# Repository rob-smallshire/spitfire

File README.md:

# SPItFIRE

**SPI + joystick FIRE button** - An analogue joystick and quadrature mouse adapter for the Acorn BBC Master Compact.

## Overview

The Acorn BBC Master Compact lacks the analogue-to-digital converter (ADC) hardware found in other BBC Micro models, making it incompatible with standard analogue joysticks. SPItFIRE bridges this gap by providing:

- **Analogue joystick support** via ADC sampling of potentiometer positions
- **Peripheral DE-9 port** for connecting a quadrature mouse (or other devices)
- **Keyboard matrix scanning** for joystick buttons

The system uses an ATMega1284p microcontroller as an SPI slave device. The BBC Master Compact's Mouse/Joystick port (an exposed 6522 VIA) communicates with the microcontroller via a bit-banged SPI protocol.

## Architecture

```
                               Host DE-9
┌─────────────────────┐         SPI          ┌──────────────────────┐
│  BBC Master Compact │◄────────────────────►│     ATMega1284p      │
│                     │   (bit-banged on     │                      │
│  6522 VIA Port      │    User VIA Port B)  │  ┌────────────────┐  │
└─────────────────────┘                      │  │ ADC: Joystick  │  │
                                             │  │ GPIO: Buttons  │  │
                                             │  │ GPIO: Mouse    │  │
                                             │  └────────────────┘  │
                                             └──────────────────────┘
                                                      │
                       ┌──────────────────────┬───────┴───────┐
                       ▼                      ▼               ▼
                 ┌──────────┐          ┌──────────┐   ┌──────────────┐
                 │ Joystick │          │  Keypad  │   │ Peripheral   │
                 │ (Analog) │          │  Matrix  │   │    DE-9      │
                 │  DA-15   │          │          │   │ Mouse/Serial │
                 └──────────┘          └──────────┘   └──────────────┘
```

## Repository Structure

```
spitfire/
├── firmware/           ATMega1284p C++ firmware (SPI slave)
│   ├── src/            Source files
│   ├── include/        Header files
│   ├── cmake/          CMake toolchain files
│   ├── CMakeLists.txt  Build configuration
│   └── CMakePresets.json
├── rom/                BBC Micro 6502 assembly ROM driver
│   └── src/            BeebAsm source files
├── hardware/           KiCAD hardware designs
│   └── spitfire/       Main schematic and PCB
└── docs/               Documentation
    └── protocol.md     SPI protocol specification
```

## Building

### Firmware (ATMega1284p)

Requirements:
- CMake 3.20+
- avr-gcc toolchain
- avrdude (for programming)

```bash
cd firmware
cmake --preset release
cmake --build --preset release
cmake --build --preset release --target upload
```

### ROM (BBC Micro)

Requirements:
- BeebAsm assembler

```bash
cd rom
make
```

## Hardware

The hardware design is created in KiCAD. See the `hardware/` directory for schematics and PCB layouts.

### Connectors

SPItFIRE has two DE-9 connectors:

- **Host DE-9**: Connects to BBC Master Compact's Mouse/Joystick port (exposes 6522 VIA). Carries SPI bus signals and device selection.
- **Peripheral DE-9**: Directly connects input devices to SPItFIRE. Directly accepts quadrature mice, switched joysticks, or serial devices. Connected to AVR Port D.

### Additional Connections

- **Joystick Inputs**: Two DA-15 ports for analogue joysticks (directly via ADC channels)

## Protocol

The BBC Micro bit-bangs an SPI protocol on the VIA port to:
- Configure the adapter
- Request joystick position data (X/Y axes)
- Request mouse velocity data
- Read button states

See [docs/protocol.md](docs/protocol.md) for the full protocol specification.

## License

This project is licensed under the GNU General Public License v3.0 - see the [LICENSE](LICENSE) file for details.

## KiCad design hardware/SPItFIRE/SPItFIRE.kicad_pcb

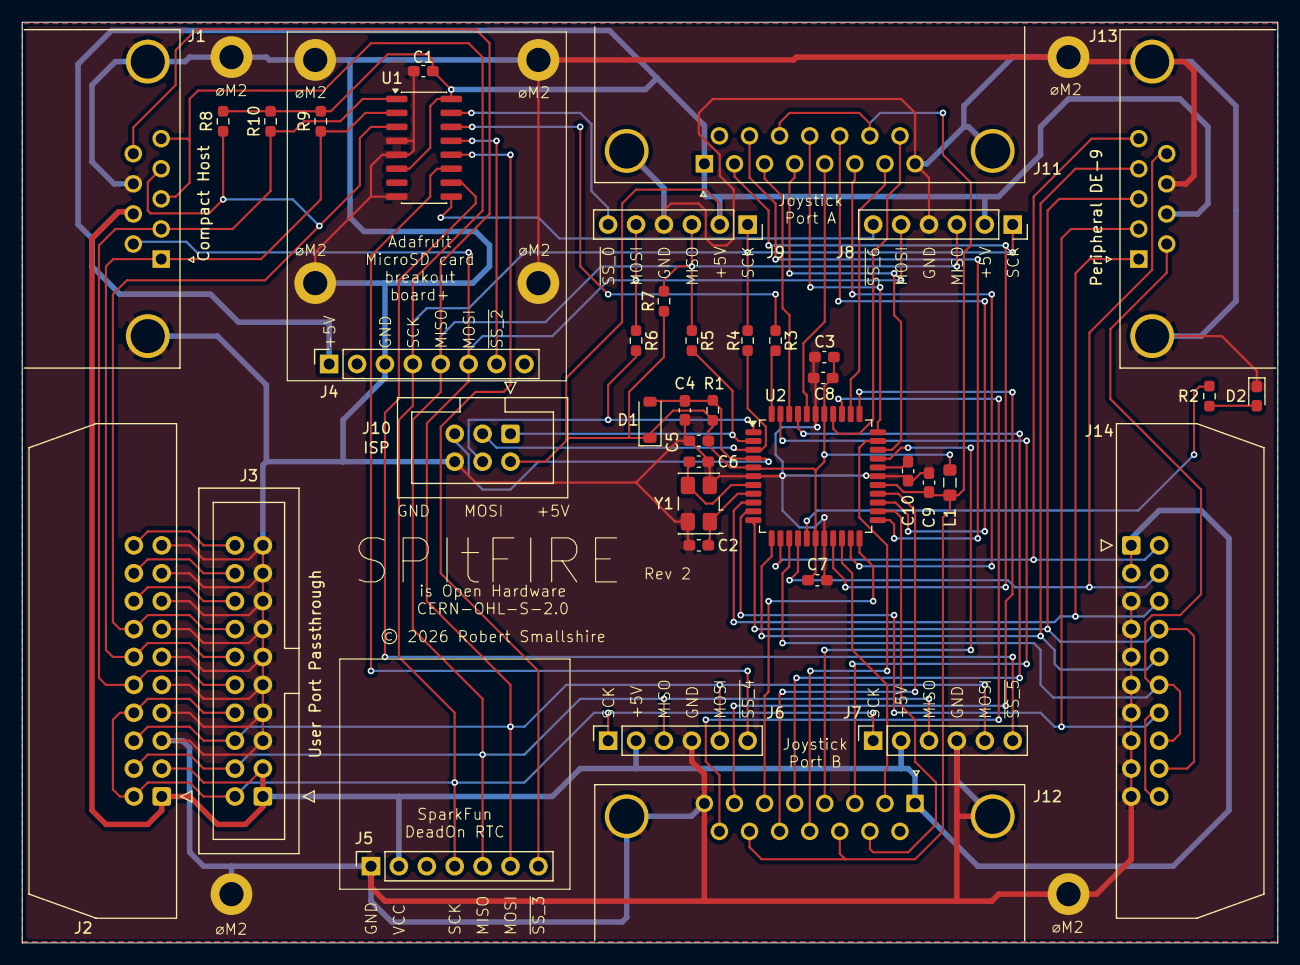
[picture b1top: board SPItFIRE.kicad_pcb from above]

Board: 2 copper layers, 114.3 x 83.8 mm, 48 parts (0 on the bottom side), 56 nets.

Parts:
C1, C4, C5, C7, C8, C9, C10: 100nF; C_0603_1608Metric_Pad1.08x0.95mm_HandSolder
C2, C6: 27pF; C_0603_1608Metric_Pad1.08x0.95mm_HandSolder
C3: 10uF; C_0603_1608Metric_Pad1.08x0.95mm_HandSolder
D1: 1N4148W; D_SOD-123
D2: LED; LED_0603_1608Metric_Pad1.05x0.95mm_HandSolder
H301, H302, H303, H304, H305, H306, H307, H308: MountingHole_Pad; MountingHole_2.2mm_M2_DIN965_Pad
J1: Compact Host; DE9_Female_Horizontal_P2.74x2.84mm_EdgePinOffset10.40mm_Hou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
J2: User Port Host; IDC-Header_2x10_P2.54mm_Latch_Horizontal
J3: User Port Passthrough; IDC-Header_2x10_P2.54mm_Vertical
J4: SD Card Adapter; PinSocket_1x08_P2.54mm_Vertical
J5: DeadOnRTC; PinSocket_1x07_P2.54mm_Vertical
J6: SPI_4; PinSocket_1x06_P2.54mm_Vertical
J7: SPI_5; PinSocket_1x06_P2.54mm_Vertical
J8: SPI_6; PinSocket_1x06_P2.54mm_Vertical
J9: SPI_7; PinSocket_1x06_P2.54mm_Vertical
J10: ISP; IDC-Header_2x03_P2.54mm_Vertical
J11: Joystick A; DA15_Female_Horizontal_P2.74x2.84mm_EdgePinOffset10.40mm_Ho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
J12: Joystick B; DA15_Female_Horizontal_P2.74x2.84mm_EdgePinOffset10.40mm_Ho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
J13: Peripheral DE-9; DE9_Male_Horizontal_P2.74x2.84mm_EdgePinOffset10.40mm_House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
J14: Peripheral User Port; IDC-Header_2x10_P2.54mm_Latch_Horizontal
L1: 10uH; L_0805_2012Metric_Pad1.05x1.20mm_HandSolder
R1, R7: 10K; R_0603_1608Metric_Pad0.98x0.95mm_HandSolder
R2: 560R; R_0603_1608Metric_Pad0.98x0.95mm_HandSolder
R3, R4, R5, R6: 1K; R_0603_1608Metric_Pad0.98x0.95mm_HandSolder
R8, R9, R10: 100K; R_0603_1608Metric_Pad0.98x0.95mm_HandSolder
U1: 74HC138; SOIC-16_3.9x9.9mm_P1.27mm
U2: ATmega1284P-A; TQFP-44_10x10mm_P0.8mm
Y1: Crystal; Crystal_SMD_5032-4Pin_5.0x3.2mm

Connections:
+5V: C1.1, C3.1, C5.1, C7.1, C8.1, D1.1 (K), J1.7, J2.1, J2.3, J3.1, J3.3, J4.1, J5.2, J6.2, J7.2, J8.2, J9.2, J10.2, J11.1, J12.1, J13.7, J14.1, J14.3, L1.1, R1.1, R7.1, R8.1, R9.1, R10.1, U1.6 (E2), U1.16 (VCC), U2.5 (VCC1), U2.17 (VCC2), U2.38 (VCC3)
/main/A0: J1.2, J2.10, J3.10, R10.2, U1.1 (A0)
/main/A1: J1.1, J2.12, J3.12, R9.2, U1.2 (A1)
/main/A2: J1.4, J2.14, J3.14, R8.2, U1.3 (A2)
/main/AVR_MISO: J10.1, R5.2, U2.2 (PB6)
/main/AVR_MOSI: J10.4, R6.2, U2.1 (PB5)
/main/AVR_SCK: J10.3, R4.2, U2.3 (PB7)
/main/~AVR_SS: R3.2, U2.44 (PB4)
AVCC: C9.1, J11.11 (P111), J11.14, J12.11 (P111), J12.14, L1.2, U2.27 (AVCC)
GND: C1.2, C2.2, C3.2, C4.2, C5.2, C6.2, C7.2, C8.2, C9.2, C10.2, D2.1 (K), H301.1 (1_1), H302.1 (1_1), H303.1 (1_1), H304.1 (1_1), H305.1 (1_1), H306.1 (1_1), H307.1 (1_1), H308.1 (1_1), J1.8, J1.SH (PAD), J2.5, J2.7, J2.9, J2.11, J2.13, J2.15, J2.17, J2.19, J3.5, J3.7, J3.9, J3.11, J3.13, J3.15, J3.17, J3.19, J4.3, J5.1, J6.4, J7.4, J8.4, J9.4, J10.6, J11.8, J11.SH (PAD), J12.8, J12.SH (PAD), J13.8, J13.SH (PAD), J14.5, J14.7, J14.9, J14.11, J14.13, J14.15, J14.17, J14.19, U1.4 (~E0), U1.5 (~E1), U1.8 (GND), U2.6 (GND1), U2.18 (GND2), U2.28 (GND4), U2.39 (GND3), Y1.2 (G), Y1.4 (G)
MISO: J1.9, J2.4, J3.4, J4.5, J5.5, J6.3, J7.3, J8.3, J9.3, R5.1, R7.2
MOSI: J1.6, J2.6, J3.6, J4.6, J5.6, J6.5, J7.5, J8.5, J9.5, R6.1
unnamed: D2.2 (A), R2.2
unnamed: J2.16, J3.16
unnamed: J2.18, J3.18
unnamed: J2.20, J3.20
unnamed: R2.1, U2.16 (PD7)
unnamed: C2.1, U2.8 (XTAL1), Y1.1
unnamed: C6.1, U2.7 (XTAL2), Y1.3
unnamed: C10.1, U2.29 (AREF)
PA0: J11.15, U2.37 (PA0)
PA1: J12.15, U2.36 (PA1)
PA2: J11.7, U2.35 (PA2)
PA3: J12.7, U2.34 (PA3)
PA4: J11.12, U2.33 (PA4)
PA5: J12.12, U2.32 (PA5)
PA6: J11.4, U2.31 (PA6)
PA7: J12.4, U2.30 (PA7)
PB0: J11.5, U2.40 (PB0)
PB1: J12.5, U2.41 (PB1)
PB2: J11.3, U2.42 (PB2)
PB3: J12.3, U2.43 (PB3)
PC0: J11.2, U2.19 (PC0)
PC1: J12.2, U2.20 (PC1)
PC2: J11.6, U2.21 (PC2)
PC3: J12.6, U2.22 (PC3)
PC4: J11.10, U2.23 (PC4)
PC5: J12.10, U2.24 (PC5)
PC6: J11.13, U2.25 (PC6)
PC7: J12.13, U2.26 (PC7)
PD0: J13.1, J14.6, U2.9 (PD0)
PD1: J13.2, J14.14, J14.20, U2.10 (PD1)
PD2: J13.3, J14.8, J14.18, U2.11 (PD2)
PD3: J13.4, J14.10, U2.12 (PD3)
PD4: J13.5, J14.2, U2.13 (PD4)
PD5: J13.6, J14.12, J14.16, U2.14 (PD5)
PD6: J13.9, J14.4, U2.15 (PD6)
SCK: J1.3, J1.5, J2.2, J2.8, J3.2, J3.8, J4.4, J5.4, J6.1, J7.1, J8.1, J9.1, R4.1
~AVR_RESET: C4.1, D1.2 (A), J10.5, R1.2, U2.4 (~RESET)
~SS_0: J9.6, U1.15 (~Y0)
~SS_1: R3.1, U1.14 (~Y1)
~SS_2: J4.7, U1.13 (~Y2)
~SS_3: J5.7, U1.12 (~Y3)
~SS_4: J6.6, U1.11 (~Y4)
~SS_5: J7.6, U1.10 (~Y5)
~SS_6: J8.6, U1.9 (~Y6)

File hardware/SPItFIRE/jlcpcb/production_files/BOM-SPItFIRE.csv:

Comment,Designator,Footprint,LCSC,Quantity
27pF,C6,C_0603_1608Metric_Pad1.08x0.95mm_HandSolder,,1
Peripheral User Port,J14,IDC-Header_2x10_P2.54mm_Latch_Horizontal,,1
10K,R7,R_0603_1608Metric_Pad0.98x0.95mm_HandSolder,,1
1K,R6,R_0603_1608Metric_Pad0.98x0.95mm_HandSolder,,1
100K,R8,R_0603_1608Metric_Pad0.98x0.95mm_HandSolder,,1
LED,D2,LED_0603_1608Metric_Pad1.05x0.95mm_HandSolder,,1
1N4148W,D1,D_SOD-123,,1
100K,R9,R_0603_1608Metric_Pad0.98x0.95mm_HandSolder,,1
SPI_5,J7,PinSocket_1x06_P2.54mm_Vertical,,1
DeadOnRTC,J5,PinSocket_1x07_P2.54mm_Vertical,,1
100nF,C7,C_0603_1608Metric_Pad1.08x0.95mm_HandSolder,,1
27pF,C2,C_0603_1608Metric_Pad1.08x0.95mm_HandSolder,,1
74HC138,U1,SOIC-16_3.9x9.9mm_P1.27mm,,1
SPI_6,J8,PinSocket_1x06_P2.54mm_Vertical,,1
Joystick B,J12,DA15_Female_Horizontal_P2.74x2.84mm_EdgePinOffset10.40mm_Housed_MountingHolesOffset16.66mm,,1
1K,R3,R_0603_1608Metric_Pad0.98x0.95mm_HandSolder,,1
SPI_4,J6,PinSocket_1x06_P2.54mm_Vertical,,1
100nF,C10,C_0603_1608Metric_Pad1.08x0.95mm_HandSolder,,1
ISP,J10,IDC-Header_2x03_P2.54mm_Vertical,,1
ATmega1284P-A,U2,TQFP-44_10x10mm_P0.8mm,,1
1K,R4,R_0603_1608Metric_Pad0.98x0.95mm_HandSolder,,1
10uF,C3,C_0603_1608Metric_Pad1.08x0.95mm_HandSolder,,1
User Port Host,J2,IDC-Header_2x10_P2.54mm_Latch_Horizontal,,1
Crystal,Y1,Crystal_SMD_5032-4Pin_5.0x3.2mm,,1
User Port Passthrough,J3,IDC-Header_2x10_P2.54mm_Vertical,,1
560R,R2,R_0603_1608Metric_Pad0.98x0.95mm_HandSolder,,1
100nF,C1,C_0603_1608Metric_Pad1.08x0.95mm_HandSolder,,1
Peripheral DE-9,J13,DE9_Male_Horizontal_P2.74x2.84mm_EdgePinOffset10.40mm_Housed_MountingHolesOffset12.5mm_1,,1
SD Card Adapter,J4,PinSocket_1x08_P2.54mm_Vertical,,1
10uH,L1,L_0805_2012Metric_Pad1.05x1.20mm_HandSolder,,1
100nF,C5,C_0603_1608Metric_Pad1.08x0.95mm_HandSolder,,1
100nF,C8,C_0603_1608Metric_Pad1.08x0.95mm_HandSolder,,1
1K,R5,R_0603_1608Metric_Pad0.98x0.95mm_HandSolder,,1
100K,R10,R_0603_1608Metric_Pad0.98x0.95mm_HandSolder,,1
100nF,C9,C_0603_1608Metric_Pad1.08x0.95mm_HandSolder,,1
10K,R1,R_0603_1608Metric_Pad0.98x0.95mm_HandSolder,,1
100nF,C4,C_0603_1608Metric_Pad1.08x0.95mm_HandSolder,,1
SPI_7,J9,PinSocket_1x06_P2.54mm_Vertical,,1
Compact Host,J1,DE9_Female_Horizontal_P2.74x2.84mm_EdgePinOffset10.40mm_Housed_MountingHolesOffset12.5mm,,1
Joystick A,J11,DA15_Female_Horizontal_P2.74x2.84mm_EdgePinOffset10.40mm_Housed_MountingHolesOffset16.66mm,,1

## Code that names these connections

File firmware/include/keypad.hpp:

#ifndef SPITFIRE_KEYPAD_HPP
#define SPITFIRE_KEYPAD_HPP

#include <stdint.h>
#include "joystick.hpp"

namespace keypad {

/// Initialize keypad I/O pins for Delta 14B scanning
/// New pin mapping (Even=A, Odd=B):
/// - Columns: PB0/PB1 (COL0), PB2/PB3 (COL1), PC0/PC1 (COL2)
/// - Rows: PA6/PA7 (ROW0), PC2/PC3 (ROW1), PC4/PC5 (ROW2), PC6/PC7 (ROW3)
void init();

/// Scan keypad for a specific port and return 12-bit button state
/// Button numbering: switch_number = row * 3 + column (0-11)
/// Bit N = switch N, where 0 = pressed, 1 = not pressed
/// @param port Which joystick port to scan (PORT_A or PORT_B)
/// @return 12-bit button state in lower 12 bits of uint16_t
uint16_t scan(joystick::Port port);

/// Scan keypad and return raw column data for a specific port
/// @param port Which joystick port to scan
/// @param col0 Output: ROW3:ROW2:ROW1:ROW0 for column 0 (bits 3:2:1:0)
/// @param col1 Output: ROW3:ROW2:ROW1:ROW0 for column 1
/// @param col2 Output: ROW3:ROW2:ROW1:ROW0 for column 2
void scan_raw(joystick::Port port, uint8_t* col0, uint8_t* col1, uint8_t* col2);

}  // namespace keypad

#endif  // SPITFIRE_KEYPAD_HPP

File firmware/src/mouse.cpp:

/**
 * SPItFIRE Mouse Firmware
 *
 * Reads mouse signals on Port D via pin-change interrupts (PCINT3),
 * accumulates movement deltas, and reports them over SPI.
 *
 * Port D pins are PCINT24-PCINT31, using PCMSK3/PCIE3/PCINT3_vect.
 *
 * SPI commands (from protocol.md):
 *   0x30 MOUSE_X   - returns clamped dX (int8), drains accumulator
 *   0x31 MOUSE_Y   - returns clamped dY (int8), drains accumulator
 *   0x32 MOUSE_BTN - returns button state byte
 *   0xF1 CMD_MODE_AMX   - switch to AMX/Compact pinout
 *   0xF2 CMD_MODE_AMIGA - switch to Amiga pinout
 *   0xF3 CMD_MODE_ATARI - switch to Atari pinout
 */

#include <avr/io.h>
#include <avr/interrupt.h>
#include <avr/pgmspace.h>
#include <string.h>
#include "status_led.hpp"

// Generated lookup tables (PROGMEM)
#include "mouse_tables.inc"

namespace {

    // --- SPI command codes ---
    constexpr uint8_t CMD_MOUSE_X   = 0x30;
    constexpr uint8_t CMD_MOUSE_Y   = 0x31;
    constexpr uint8_t CMD_MOUSE_BTN = 0x32;
    constexpr uint8_t CMD_MODE_AMX   = 0xF1;
    constexpr uint8_t CMD_MODE_AMIGA = 0xF2;
    constexpr uint8_t CMD_MODE_ATARI = 0xF3;

    // --- SRAM working copies of active lookup tables ---
    uint8_t remap[128];
    uint8_t btn_remap[128];

    // --- Pointers to active decode tables (in PROGMEM) ---
    const uint8_t* dx_table_ptr = quad_dx_table;
    const uint8_t* dy_table_ptr = quad_dy_table;

    // --- Pin-change interrupt mask (set per mode) ---
    uint8_t pcint_mask = 0;

    // --- Accumulators (updated by ISR) ---
    volatile int16_t dx_accum = 0;
    volatile int16_t dy_accum = 0;

    // --- ISR state ---
    uint8_t prev_state = 0;

    // --- Initialisation ---

    void init_spi_slave() {
        DDRB = (DDRB & ~(_BV(PB4) | _BV(PB5) | _BV(PB7))) | _BV(PB6);
        SPCR = _BV(SPE);
        SPDR = 0x00;
    }

    void init_mouse_pins() {
        DDRD &= ~0x7F;  // PD0-PD6 inputs (PD7 is the status LED)
        PORTD |= 0x7F;  // Pull-ups on inputs
    }

    void init_pcint() {
        PCMSK3 = pcint_mask;     // Port D uses PCMSK3 (PCINT24-31)
        PCICR |= _BV(PCIE3);    // Enable PCINT3 vector
    }

    void load_quadrature_mode(const uint8_t* pgm_remap, const uint8_t* pgm_btn,
                              uint8_t xa_pin, uint8_t xb_pin,
                              uint8_t ya_pin, uint8_t yb_pin) {
        cli();
        memcpy_P(remap, pgm_remap, 128);
        memcpy_P(btn_remap, pgm_btn, 128);
        dx_table_ptr = quad_dx_table;
        dy_table_ptr = quad_dy_table;
        // Interrupt on all four quadrature pins
        pcint_mask = _BV(xa_pin) | _BV(xb_pin) | _BV(ya_pin) | _BV(yb_pin);
        PCMSK3 = pcint_mask;
        // Initialise state
        prev_state = pgm_read_byte(&pgm_remap[PIND & 0x7F]);
        dx_accum = 0;
        dy_accum = 0;
        sei();
    }

    int8_t clamp_and_drain(volatile int16_t& accum) {
        cli();
        int16_t val = accum;
        int8_t out;
        if (val > 127) {
            out = 127;
        } else if (val < -127) {
            out = -127;
        } else {
            out = static_cast<int8_t>(val);
        }
        accum -= out;
        sei();
        return out;
    }

}  // anonymous namespace

// --- Pin Change ISR for Port D (PCINT3, not PCINT2!) ---
// Port D pins are PCINT24-31, handled by PCINT3_vect.
ISR(PCINT3_vect) {
    uint8_t curr = remap[PIND & 0x7F];
    uint8_t idx = (prev_state << 4) | curr;

    dx_accum += static_cast<int8_t>(pgm_read_byte(&dx_table_ptr[idx]));
    dy_accum += static_cast<int8_t>(pgm_read_byte(&dy_table_ptr[idx]));
    prev_state = curr;
}

int main() {
    status_led::init();
    init_mouse_pins();
    init_spi_slave();

    // Default to Compact/AMX (true quadrature, XA=PD4, XB=PD0, YA=PD6, YB=PD3)
    load_quadrature_mode(remap_compact, btn_remap_compact, PD4, PD0, PD6, PD3);

    init_pcint();

    status_led::startup_flash();
    status_led::start_heartbeat();
    sei();

    // SPI command loop
    while (true) {
        while (!(SPSR & _BV(SPIF)));

        uint8_t cmd = SPDR;
        uint8_t response;

        switch (cmd) {
            case CMD_MOUSE_X:
                response = static_cast<uint8_t>(clamp_and_drain(dx_accum));
                break;

            case CMD_MOUSE_Y:
                response = static_cast<uint8_t>(clamp_and_drain(dy_accum));
                break;

            case CMD_MOUSE_BTN:
                response = btn_remap[PIND & 0x7F];
                break;

            case CMD_MODE_AMX:
                load_quadrature_mode(remap_compact, btn_remap_compact,
                                     PD4, PD0, PD6, PD3);
                response = 0x01;
                break;

            case CMD_MODE_AMIGA:
                load_quadrature_mode(remap_amiga, btn_remap_amiga,
                                     PD1, PD3, PD2, PD0);
                response = 0x02;
                break;

            case CMD_MODE_ATARI:
                load_quadrature_mode(remap_atari, btn_remap_atari,
                                     PD1, PD0, PD2, PD3);
                response = 0x03;
                break;

            default:
                response = 0xFF;
                break;
        }

        SPDR = response;
    }
}

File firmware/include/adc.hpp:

#ifndef SPITFIRE_ADC_HPP
#define SPITFIRE_ADC_HPP

#include <stdint.h>
#include "joystick.hpp"

namespace adc {

/// ADC channel numbers (PA0-PA7)
/// Channel assignments for joystick ports:
///   X axis:      ADC0 (Port A) / ADC1 (Port B)
///   Y axis:      ADC2 (Port A) / ADC3 (Port B)
///   X_RIGHT:     ADC4 (Port A) / ADC5 (Port B) - Delta 3B Twin only
///   Y_RIGHT:     ADC6 (Port A) / ADC7 (Port B) - Delta 3B Twin only
enum class Channel : uint8_t {
    ADC0 = 0,  // PA0 - X axis (Port A)
    ADC1 = 1,  // PA1 - X axis (Port B)
    ADC2 = 2,  // PA2 - Y axis (Port A)
    ADC3 = 3,  // PA3 - Y axis (Port B)
    ADC4 = 4,  // PA4 - X_RIGHT (Port A) / detection pin
    ADC5 = 5,  // PA5 - X_RIGHT (Port B)
    ADC6 = 6,  // PA6 - Y_RIGHT (Port A) or ROW0 for Delta 14B
    ADC7 = 7   // PA7 - Y_RIGHT (Port B) or ROW0 for Delta 14B
};

/// Initialize ADC with AVCC reference and appropriate prescaler
void init();

/// Read 10-bit value from specified channel (0-1023)
uint16_t read(Channel channel);

/// Read 8-bit value from specified channel (0-255)
uint8_t read8(Channel channel);

/// Read X axis for a given joystick port
inline uint16_t read_x(joystick::Port port) {
    return read(port == joystick::Port::PORT_A ? Channel::ADC0 : Channel::ADC1);
}

/// Read Y axis for a given joystick port
inline uint16_t read_y(joystick::Port port) {
    return read(port == joystick::Port::PORT_A ? Channel::ADC2 : Channel::ADC3);
}

/// Read X_RIGHT axis for a given joystick port (Delta 3B Twin only)
inline uint16_t read_x_right(joystick::Port port) {
    return read(port == joystick::Port::PORT_A ? Channel::ADC4 : Channel::ADC5);
}

/// Read Y_RIGHT axis for a given joystick port (Delta 3B Twin only)
inline uint16_t read_y_right(joystick::Port port) {
    return read(port == joystick::Port::PORT_A ? Channel::ADC6 : Channel::ADC7);
}

}  // namespace adc

#endif  // SPITFIRE_ADC_HPP

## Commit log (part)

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2025-12-31 Add .gitignore
2025-12-31 Add project README and SPI protocol documentation
2025-12-31 Add reference datasheets
2025-12-31 Add firmware CMake build system for ATMega1284p
2025-12-31 Add LED blink test firmware on PB0
2025-12-31 Add ROM build system for BeebAsm
2025-12-31 Add hardware directory placeholder
2025-12-31 Add GitHub Actions workflow for firmware build
2026-01-01 Expand KiCad gitignore patterns
2026-01-01 Updates the README.md
2026-01-01 Schematic capture of the Voltmace Delta 14b joystick internals
2026-01-01 Adds AVR programming notes so I don't forget everything again
2026-01-03 Voltmace pinouts
2026-01-24 Update pinouts
2026-02-11 Update schematic naming convention to keep Kicad happy
2026-03-08 Add beeb/spitest/build to gitignore
2026-03-15 Fix SPI speed by disabling CB1 interrupts
    The OS leaves CB1 interrupts enabled, and since CB1 is wired to SCK,
    every clock falling edge triggered an IRQ. This caused 2048 interrupts
    per 256-byte transfer, reducing speed from ~4200 bytes/sec to ~6 bytes/sec.
    Fix: Write %00011000 to IER at start of init_via to disable CB1/CB2
    interrupts before any SPI operations.
    Also:
2026-03-15 Fix SPIPERF division algorithm
    The 24-bit / 16-bit division was producing results 256x too large
    because the dividend storage (div_tmp+0:+2) overlapped with the
    remainder comparison region (div_tmp+2:+3).
    Fix: Use 5-byte workspace with separate regions:
    - div_tmp+0:+2 = dividend (24-bit)
    - div_tmp+3:+4 = remainder (16-bit)
2026-03-16 Add turbo mode SPI tests using VIA shift register
    The VIA shift register (SR mode 3) captures MISO automatically on CB1
    edges. Since CB1 is wired to PB1 (SCK), our clock toggles trigger SR
    capture without per-bit software handling.
    New programs:
    - SPITTEST: Soak test with SR mode, verifies XOR pattern
    - SPIT256: Timing test with optimized read-only routine
2026-03-21 Add Host/Peripheral DE-9 terminology and peripheral pinouts
    Establish clear naming convention for SPItFIRE's two DE-9 connectors:
    - Host DE-9: connects to BBC Master Compact (SPI bus)
    - Peripheral DE-9: connects input devices (mice, joysticks, serial)
    Add peripheral-pinouts.md documenting pinouts for:
    - Master Compact Mouse
    - Amiga Mouse
2026-03-21 Add 74HC138 decoder datasheet
2026-03-21 Add AVR Port D mapping to peripheral pinouts
2026-03-25 Add BBC Micro User Port adapter documentation
    Document User Port to DE-9 adapter for connecting AMX Mouse and
    Marconi RB2 Trackerball to SPItFIRE. The adapter merges signals
    from both device types onto 7 DE-9 pins since only one device
    connects at a time.
    Includes verified pinouts from mdfs.net and Marconi RB2 User Guide.
    Note: adapter is SPItFIRE-specific, not directly Compact-compatible.
2026-04-02 Redesign User Port adapter with dual-purpose Compact Mouse pinout
    AMX Mouse via adapter now works both with SPItFIRE and directly
    with the Master Compact mouse port. Marconi RB2 trackerball via
    adapter requires SPItFIRE with dedicated firmware mode. Only one
    additional firmware mode needed instead of two.
2026-04-02 Add AVR Pin column to User Port adapter wiring table
2026-04-04 Add quadrature mouse firmware and BBC test program
    AVR firmware (mouse.cpp) reads quadrature mouse signals on Port D
    via pin-change interrupts, decodes movement using table-driven Gray
    code lookup, accumulates deltas, and reports over SPI commands
    0x30/0x31/0x32. Supports multiple pinouts via PROGMEM remap tables
    (Compact, Amiga, Atari, Bus Mouse, Trackerball).
    BBC test program (SPIMOUSE) polls at 100 Hz via centisecond timer,
2026-04-04 Add __pycache__ to .gitignore
2026-04-05 The bulk of the schematic layout for the board (pending review and check)
2026-04-19 Fix PCINT vector for Port D and add runtime mode switching
    Port D on ATMega1284P uses PCINT24-31 (PCINT3 group), not PCINT16-23
    (PCINT2) as previously assumed. Fixed to use PCMSK3/PCIE3/PCINT3_vect.
    Also fixed quadrature decode table column ordering (numerical order,
    not Gray code order).
    Added SPI commands 0xF1/0xF2/0xF3 for runtime pinout switching
    between AMX, Amiga, and Atari mice. BBC test program SPIMOUSE now
2026-04-20 Fix Amiga mouse Y-axis pin assignment (YA/YB were swapped)
    DE-9 Pin 1 is YB (not YA) and Pin 3 is YA (not YB) for the Amiga
    mouse. Verified with actual Amiga mouse hardware - Y axis was
    reversed before this fix. Corrected in pinout tables, remap table
    generator, and firmware mode switching.
2026-04-25 Fix Amiga/Atari comparison: only pins 1 and 4 differ, not 1, 3, and 4
2026-04-25 Document MDFS Y-axis label convention difference
    The Amiga/Atari pinouts on mdfs.net reverse the Y-axis signal
    labels (YA/YB) relative to native conventions, to match BBC Micro
    coordinate system handedness. Our pinout table uses native Amiga/
    Atari conventions. This note prevents future confusion when
    cross-referencing MDFS as a source.
2026-04-25 Pin nomenclature
2026-04-25 Schematic updates
2026-04-25 Schematic updates and rule checking
2026-04-26 ERC exclusions
2026-04-27 ERC warnings and labels
2026-04-30 Add SPItFIRE ROM design proposal document
2026-04-30 Add ADVAL(5)/ADVAL(6) mouse boundary calls to ROM design
2026-04-30 Add SPITFIRE command namespace and OSWORD &40 button format details
    Introduces *SPITFIRE command hierarchy for SPItFIRE-specific
    configuration, mirroring the modular ROM structure (MOUSE, JOYSTICK,
    RTC, SD subcommands). Standard commands (*MOUSE, *TIME etc.) remain
    in their established namespaces for ecosystem compatibility.
    Documents the OSWORD &40 byte-6 button format (cme00000, active-low)
    which differs from ADVAL(9) (active-high in bits 0-2). Adds reference
2026-04-30 Document mouse coordinate systems and BBC bottom-left graphics origin
2026-04-30 Master Compact welcome disc
2026-04-30 AMX Mouse User Guide
2026-06-23 Work on the schematic and the beginnings of footprint assignment
2026-06-23 Track CLAUDE.md and update with current repo layout and architecture notes

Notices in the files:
hardware/SPItFIRE/SPItFIRE.kicad_pcb:
© 2026 Robert Smallshire
CERN-OHL-S-2.0
